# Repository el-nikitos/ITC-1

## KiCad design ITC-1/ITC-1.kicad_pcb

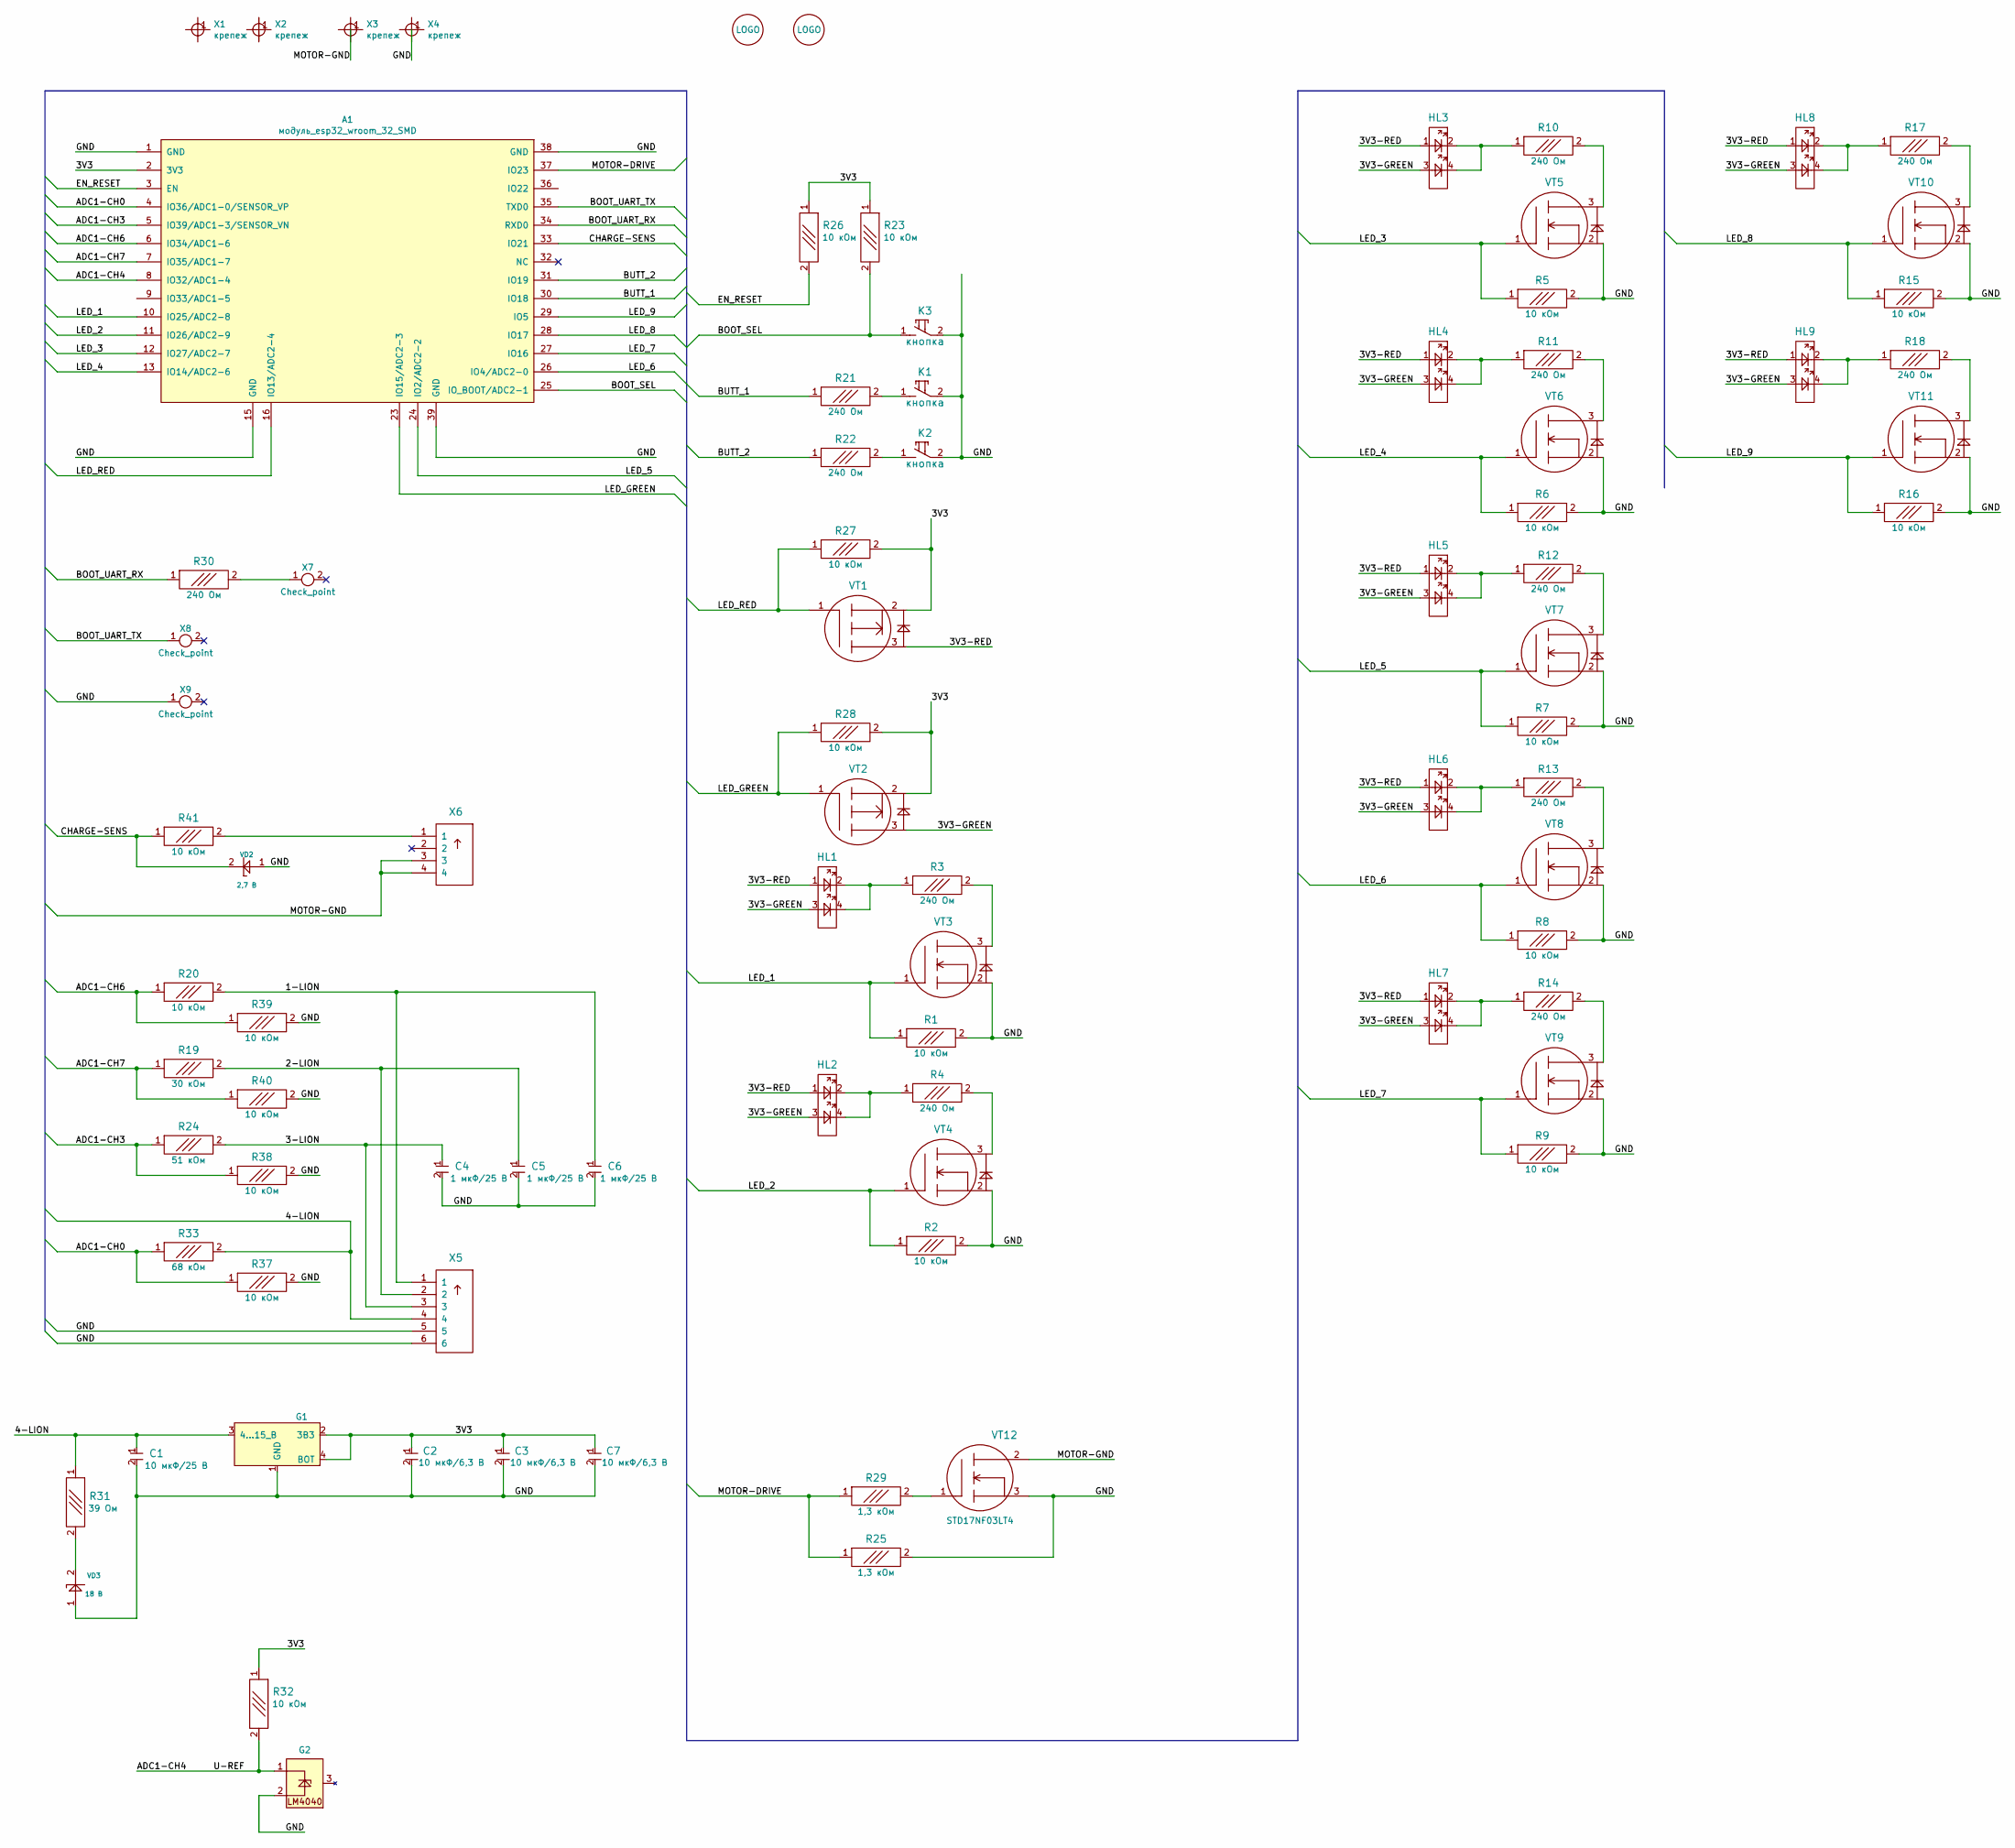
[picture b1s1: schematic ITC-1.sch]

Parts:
A1: модуль_esp32_wroom_32_SMD; ESP32_WROOM32_pnp_noSD
C1: Конденсатор_керамический; Конденсатор_SMD_IEC_0805
C2, C3, C4, C5, C6, C7: Конденсатор_керамический; Конденсатор_SMD_0603_pnp
D1: LOGO; ni_10x10
D2: LOGO; VLAD_10x10
G1: стабилизатор_нерегулируемый_LM1117S33; Транзистор_NPN_SOT223_pnp
G2: ИОП_LM4040BIM3-2.5_NOPB; Корпус_КТ-46
HL1, HL2, HL3, HL4, HL5, HL6, HL7, HL8, HL9: Светодиод_сдвоенный_KPB-3025SURKCGKC; Светодиод_SMD_m3025
K1, K2, K3: кнопка; Кнопка_FSMSM
R1, R2, R3, R4, R5, R6, R7, R8, R9, R10, R11, R12, R13, R14, R15, R16, R17, R18, R19, R20, R21, R22, R23, R24, R25, R26, R27, R28, R29, R30, R31, R32, R33, R37, R38, R39, R40, R41: Резистор_0,065Вт; Резистор_SMD_0603_0,065_Вт_pnp
VD2, VD3: Стабилитрон_1N5352BRLG_вертикальный; SOD-80
VT1, VT2: Транзистор_полевой_P-канал(IRLML2246TRPBF); Транзистор_IRLML6344TR_SOT-23
VT3, VT4, VT5, VT6, VT7, VT8, VT9, VT10, VT11: Транзистор_полевой_N-IRLML6344TR; Транзистор_IRLML6344TR_SOT-23
VT12: Транзистор_полевой_N-канал; Транзистор_N-канал_dpak_DS
X1, X2: крепеж; Отверстие_М3
X3, X4: крепеж; ОтверстиеD1.2
X5: Вилка_PLS6; Вилка_PLD6_вертикальная
X6: Вилка_PLS4; Вилка_PLD4_вертикальная
X7, X8, X9: Check_point; Пробник

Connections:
/1-LION: C6.1, R20.2, X5.1
/2-LION: C5.1, R19.2, X5.2
/3-LION: C4.1, R24.2, X5.3
/3V3: A1.2 (3V3), C2.1, C3.1, C7.1, G1.2 (3В3), G1.4 (BOT), R23.1, R26.1, R27.2, R28.2, R32.1, VT1.2, VT2.2
/3V3-GREEN: HL1.3, HL2.3, HL3.3, HL4.3, HL5.3, HL6.3, HL7.3, HL8.3, HL9.3, VT2.3
/3V3-RED: HL1.1, HL2.1, HL3.1, HL4.1, HL5.1, HL6.1, HL7.1, HL8.1, HL9.1, VT1.3
/4-LION: C1.1, G1.3 (4...15_В), R31.1, R33.2, X5.4
/ADC1-CH0: A1.4 (IO36/ADC1-0/SENSOR_VP), R33.1, R37.1
/ADC1-CH3: A1.5 (IO39/ADC1-3/SENSOR_VN), R24.1, R38.1
/ADC1-CH4: A1.8 (IO32/ADC1-4), G2.1, R32.2
/ADC1-CH6: A1.6 (IO34/ADC1-6), R20.1, R39.1
/ADC1-CH7: A1.7 (IO35/ADC1-7), R19.1, R40.1
/BOOT_SEL: A1.25 (IO_BOOT/ADC2-1), K3.1, R23.2
/BOOT_UART_RX: A1.34 (RXD0), R30.1
/BOOT_UART_TX: A1.35 (TXD0), X8.1
/BUTT_1: A1.30 (IO18), R21.1
/BUTT_2: A1.31 (IO19), R22.1
/CHARGE-SENS: A1.33 (IO21), R41.1, VD2.2
/EN_RESET: A1.3 (EN), R26.2
/GND: A1.1 (GND), A1.15 (GND), A1.38 (GND), A1.39 (GND), C1.2, C2.2, C3.2, C4.2, C5.2, C6.2, C7.2, G1.1 (GND), G2.2, K1.2, K2.2, K3.2, R1.2, R2.2, R5.2, R6.2, R7.2, R8.2, R9.2, R15.2, R16.2, R25.2, R37.2, R38.2, R39.2, R40.2, VD2.1, VD3.1, VT3.2, VT4.2, VT5.2, VT6.2, VT7.2, VT8.2, VT9.2, VT10.2, VT11.2, VT12.3, X4.1, X5.5, X5.6, X9.1
/LED_1: A1.10 (IO25/ADC2-8), R1.1, VT3.1
/LED_2: A1.11 (IO26/ADC2-9), R2.1, VT4.1
/LED_3: A1.12 (IO27/ADC2-7), R5.1, VT5.1
/LED_4: A1.13 (IO14/ADC2-6), R6.1, VT6.1
/LED_5: A1.24 (IO2/ADC2-2), R7.1, VT7.1
/LED_6: A1.26 (IO4/ADC2-0), R8.1, VT8.1
/LED_7: A1.27 (IO16), R9.1, VT9.1
/LED_8: A1.28 (IO17), R15.1, VT10.1
/LED_9: A1.29 (IO5), R16.1, VT11.1
/LED_GREEN: A1.23 (IO15/ADC2-3), R28.1, VT2.1
/LED_RED: A1.16 (IO13/ADC2-4), R27.1, VT1.1
/MOTOR-DRIVE: A1.37 (IO23), R25.1, R29.1
/MOTOR-GND: VT12.2, X3.1, X6.3, X6.4
unnamed: HL1.2, HL1.4, R3.1
unnamed: HL2.2, HL2.4, R4.1
unnamed: HL3.2, HL3.4, R10.1
unnamed: HL4.2, HL4.4, R11.1
unnamed: HL5.2, HL5.4, R12.1
unnamed: HL6.2, HL6.4, R13.1
unnamed: HL7.2, HL7.4, R14.1
unnamed: HL8.2, HL8.4, R17.1
unnamed: HL9.2, HL9.4, R18.1
unnamed: K1.1, R21.2
unnamed: K2.1, R22.2
unnamed: R3.2, VT3.3
unnamed: R4.2, VT4.3
unnamed: R10.2, VT5.3
unnamed: R11.2, VT6.3
unnamed: R12.2, VT7.3
unnamed: R13.2, VT8.3
unnamed: R14.2, VT9.3
unnamed: R17.2, VT10.3
unnamed: R18.2, VT11.3
unnamed: R29.2, VT12.1
unnamed: R30.2, X7.1
unnamed: R31.2, VD3.2
unnamed: R41.2, X6.1

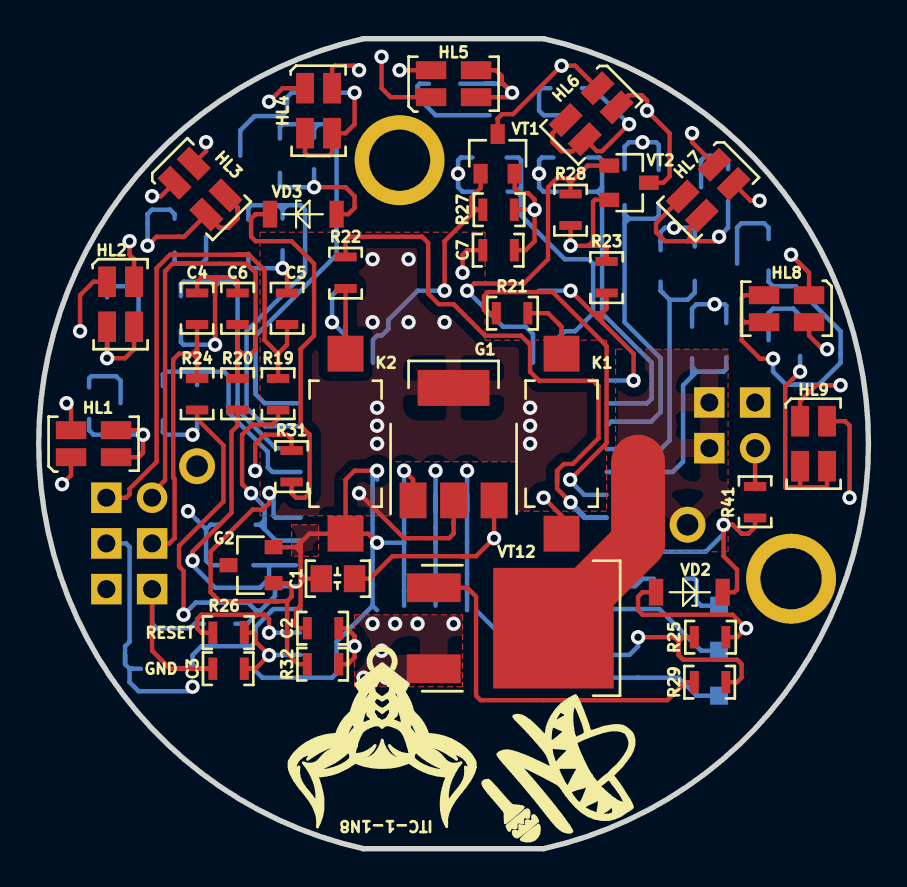
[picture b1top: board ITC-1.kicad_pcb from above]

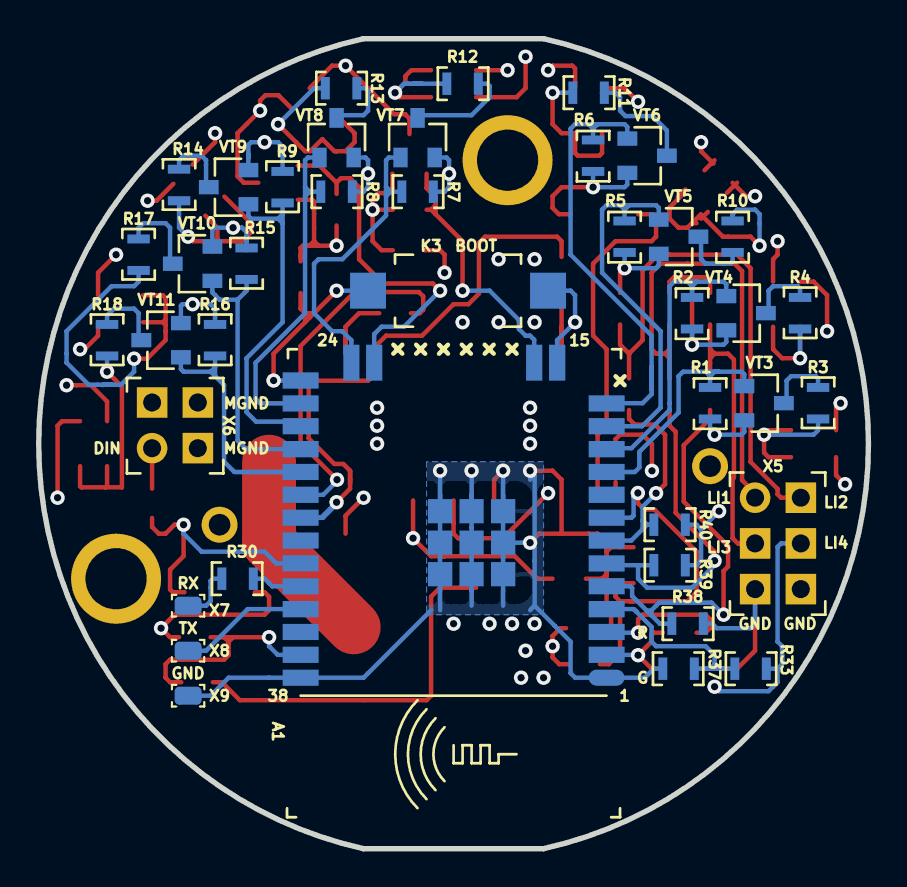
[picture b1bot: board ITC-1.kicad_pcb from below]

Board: 4 copper layers, 46.1 x 45.0 mm, 85 parts (40 on the bottom side), 57 nets.

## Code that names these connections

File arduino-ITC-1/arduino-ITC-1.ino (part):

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#include <WiFiClient.h>
#include <WiFiAP.h>

#define LED_RED     13
#define LED_GREEN   15
#define LED_9       25
#define LED_8       26
#define LED_7       27
#define LED_6       14
#define LED_5       2
#define LED_4       4
#define LED_3       16
#define LED_2       17
#define LED_1       5
#define DRIVE       21//23
#define BTN_R       19
#define BTN_L       18
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
  adc_read();

  blink_pin( LED_1 );
  blink_pin( LED_2 );
  blink_pin( LED_3 );
  blink_pin( LED_4 );
  blink_pin( LED_5 );
  blink_pin( LED_6 );
  blink_pin( LED_7 );
  blink_pin( LED_8 );
  blink_pin( LED_9 );

  ledcSetup( int_pwm_channel, int_pwm_freq, int_pwm_resolution );
  ledcAttachPin( DRIVE, int_pwm_channel );
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}

void init_pins()  {
  pinMode( LED_RED, OUTPUT );
  digitalWrite( LED_RED, HIGH );
  
  pinMode( LED_GREEN, OUTPUT );
  digitalWrite( LED_GREEN, HIGH );
  
  pinMode( LED_1, OUTPUT );
  digitalWrite( LED_1, LOW );

  pinMode( LED_2, OUTPUT );
  digitalWrite( LED_2, LOW );

  pinMode( LED_3, OUTPUT );
  digitalWrite( LED_3, LOW );

  pinMode( LED_4, OUTPUT );
  digitalWrite( LED_4, LOW );

  pinMode( LED_5, OUTPUT );
  digitalWrite( LED_5, LOW );

  pinMode( LED_6, OUTPUT );
  digitalWrite( LED_6, LOW );

  pinMode( LED_7, OUTPUT );
  digitalWrite( LED_7, LOW );

  pinMode( LED_8, OUTPUT );
  digitalWrite( LED_8, LOW );

  pinMode( LED_9, OUTPUT );
  digitalWrite( LED_9, LOW );

  pinMode( DRIVE, OUTPUT );
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
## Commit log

2021-05-10 определено расположение основных элементов и габарит
2021-05-16 расположено управление светодиодами
2021-05-23 заменены разъемы, исключены ОУ, определена распиновка и упр. транзистор
2021-05-24 определено подключение аналоговых входов
2021-05-25 упрощена схема подтяжек, раскинут разъем программирования
2021-05-29 раскинуты все разъемы, требуется подключить LED и поставить лого
2021-05-29 готова трассировка, требуется контрольная проверка
2021-05-30 добавлено отверстие для бондажа, требуется заменить светодиоды
2021-06-02 заменены светодиоды на сдвоенные
2021-06-03 закончена трассировка, сформированы герберы
2021-06-04 исправлено заземление транзистора, подготовлены файлы производства
2021-06-21 определены номиналы делителей, добавлены ссылки на чип и дип
2021-06-27 проект для схемы внешних подключений
2021-06-27 обновлена PDF, добавлены элементы платы на схеме внешних подключений
2021-06-27 обновлена верхняя схема
2021-06-27 подготовлена схема внешних подключений
2021-08-11 arduino test: оцифровка, кнопки, светодиоды, шим - не систематизировано
2021-08-15 arduino: задержка запуска и выключение по таймауту
2021-08-15 PCB: транзистор N-канал, утолщены дорожки, кнопка BOOT, заменен прог.
2021-08-17 ITC-1-1 исправлен проект
    добавлены стабилизаторы на DIN и LI4, усилены дорожки, фаски с двух сторон
2021-08-17 на esp32 убраны запрещенные площадки, сформированы gerber-файлы
2021-08-22 обновлена номенклатура для заказа ПКИ
2021-08-30 изменена индикация выбора скорости, добавлен перевод напряжения в заряд
2021-09-02 дополнительная индикация при низком заряде
2021-10-08 время работы движка - 60 сек, ШИМ - 150 Гц, при заряде led всегда мигают
2021-10-08 ШИМ 200 Гц, при заряде поочередно мигает текущее деление и следующее
2021-10-17 обновлены УГО ESP и список цепей
2021-10-24 WiFi AP + сервер и подсчет подключенных клиентов
2021-10-27 парсер приема по wifi.client; своё условие при наличии подсоединения
2021-10-28 реализовано включение/выключение по посылке start/stop
2021-12-19 добавлены команды speed++ и speed--
2022-01-23 обновлено УГО для внешнего подключения
2022-03-21 переведена работа с коллекторного движка на синхронный
2022-04-21 изменены частотные характеристики
